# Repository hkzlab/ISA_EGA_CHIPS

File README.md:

# Enhanced Graphics Adapter

## Introduction

This board is and EGA clone based on a reversed **PA-WTEGA** card, based on the chipset by **CHIPS** (P82C435 + P82A436). 

The chipset should be compatible with EGA, CGA, MDA and Hercules standards.

### Disclaimer

I take NO responsibility for what happens if you decide to build and use this card. Your computer might crash, catch fire or be destroyed in other nasty ways.
You're encourauged to take what you deem fit from this, and use it in your projects!

### Configuration

The card as a bank of 5 dipswitches. Dipswitch 1-4 select the card video output mode, dipswitch 5 selects the IO address.

0 means switch open, 1 means closed.

* Jumpers 1-4:
    * 0-1-0-0: MDA Mode (main)
    * 1-0-0-1: CGA 40x25 (main)
    * 1-0-0-0: CGA 80x25 (main)
    * 0-1-1-1: EGA 200 lines (main)
    * 0-1-1-0: EGA 350 lines (main)
    * 1-1-1-1: CGA 40x25 (secondary)
    * 1-1-1-0: CGA 80x25 (secondary)
    * 1-1-0-1: EGA 200 lines (secondary)
    * 1-1-0-0: EGA 350 lines (secondary)
* Jumper 5:
    * 0: I/O address range in 3xx **default**
    * 1: I/O address range in 2xx

**NOTE:** The meaning of each combination is dependant on the bios of the card. This list was taken from the TEVA-2 card's manual.

TODO: Test all the combinations provided in the TEVA-2 card manual

### Functionalities

✅ means I tested the functionality and it works, ❌ means I tested the functionality and found issues, ? means that the functionality has yet to be tested.

* [✅] Display checkup with CheckIt (5154/EGA monitor)
* [✅] Display checkup with CheckIt (5153/CGA monitor)
* [?] Display checkup with CheckIt (5151/MDA monitor)
* [?] Display checkup with CheckIt (Hercules mode)
* [?] Feature Connector
* [?] Light pen input

## Bill of Materials

| Component         | Qty | Type / Value        |
| ----------------- | --- | ------------------- |
| **TODO**          |     |                     |

You can hardwire `JP1` pins 1-2 and `JP2` pins 2-3.

Connectors `RCA 1` and `RCA 2` are useless unless an expansion for the feature connector is used. You can leave them out.

### BIOS

This board was tested with [Phoenix Video Bios V1.02 for P82C435](bios/Phoenix_video_bios_PA-WTEGA_NMC27C256Q.BIN).

Burn it on a 27C256 and plug it in U10.

### Component substitutions

* U15 and U13 can be substituted with HCT equivalents
* U4 is an 'LS244 in the original card, I noticed an improvement in image stability with a MCE2VGA by using an 'F244 

## Known issues

### General issues

These are issues found with this board, but that are **also present in the original model** I cloned.

* Screen tearing detected in Commander Keen 4 and 5 (also happening on DOSBox configured for EGA, also note [here](http://nerdlypleasures.blogspot.com/2014/09/how-many-fps-dos-games-and-framerates.html): `The use of 35 frames, even in a 16-color game like Keen, demonstrates that ID was using VGA, not EGA, to develop the game` ). It can be fixed in-game by enabling the "Fix Jerky Motion" option in the config screen.
* Minor graphical glitches (flickering at top of the screen) during gameplay in Tom & Jerry CAT-astrophe.

### Rev 0.1

* Not really an issue as this is not present in the original card I cloned, but might be worth to add a jumper that can physically connect pin 2 of the DB9 connector to GND and not rely only on the jumper configuration, when using the card with a CGA monitor.

### Rev 0

* Some traces stub are left near the edge connector
* Some traces for sensitive sync signals are routed under the oscillators

## TODO

* Testing...

## Credits

Thanks to [Sergey Kiselev](https://github.com/skiselev) for his symbol/footprint library!

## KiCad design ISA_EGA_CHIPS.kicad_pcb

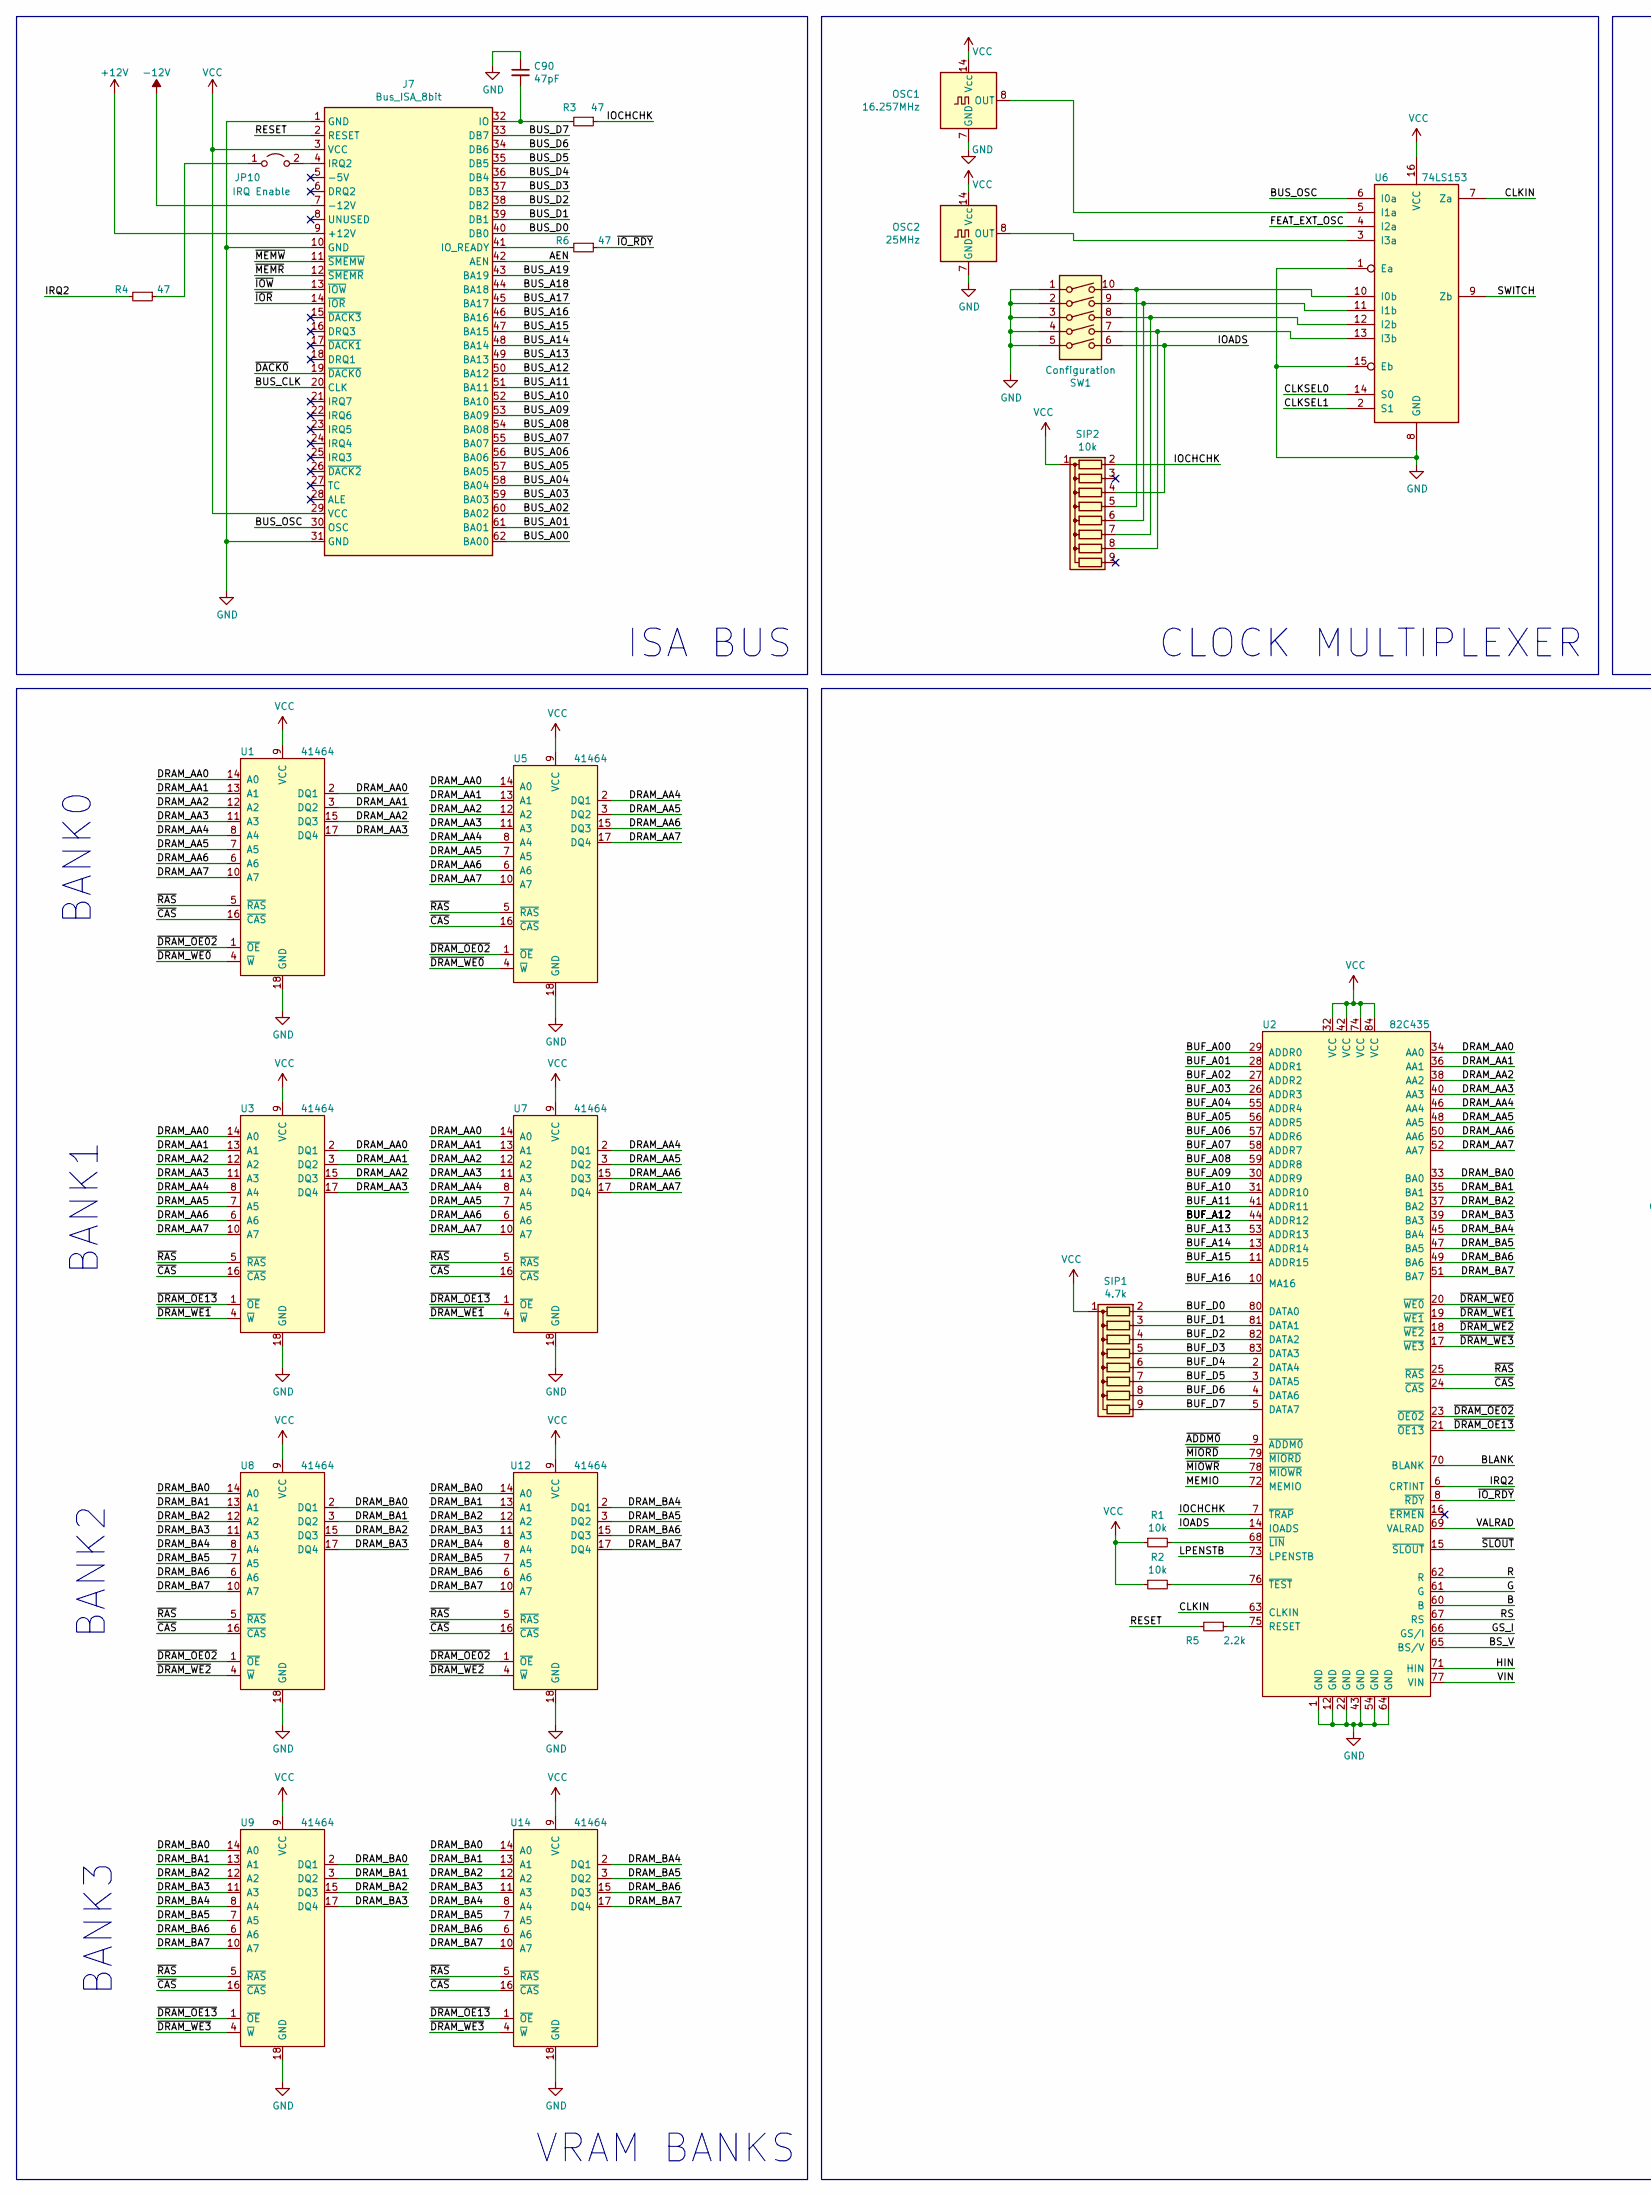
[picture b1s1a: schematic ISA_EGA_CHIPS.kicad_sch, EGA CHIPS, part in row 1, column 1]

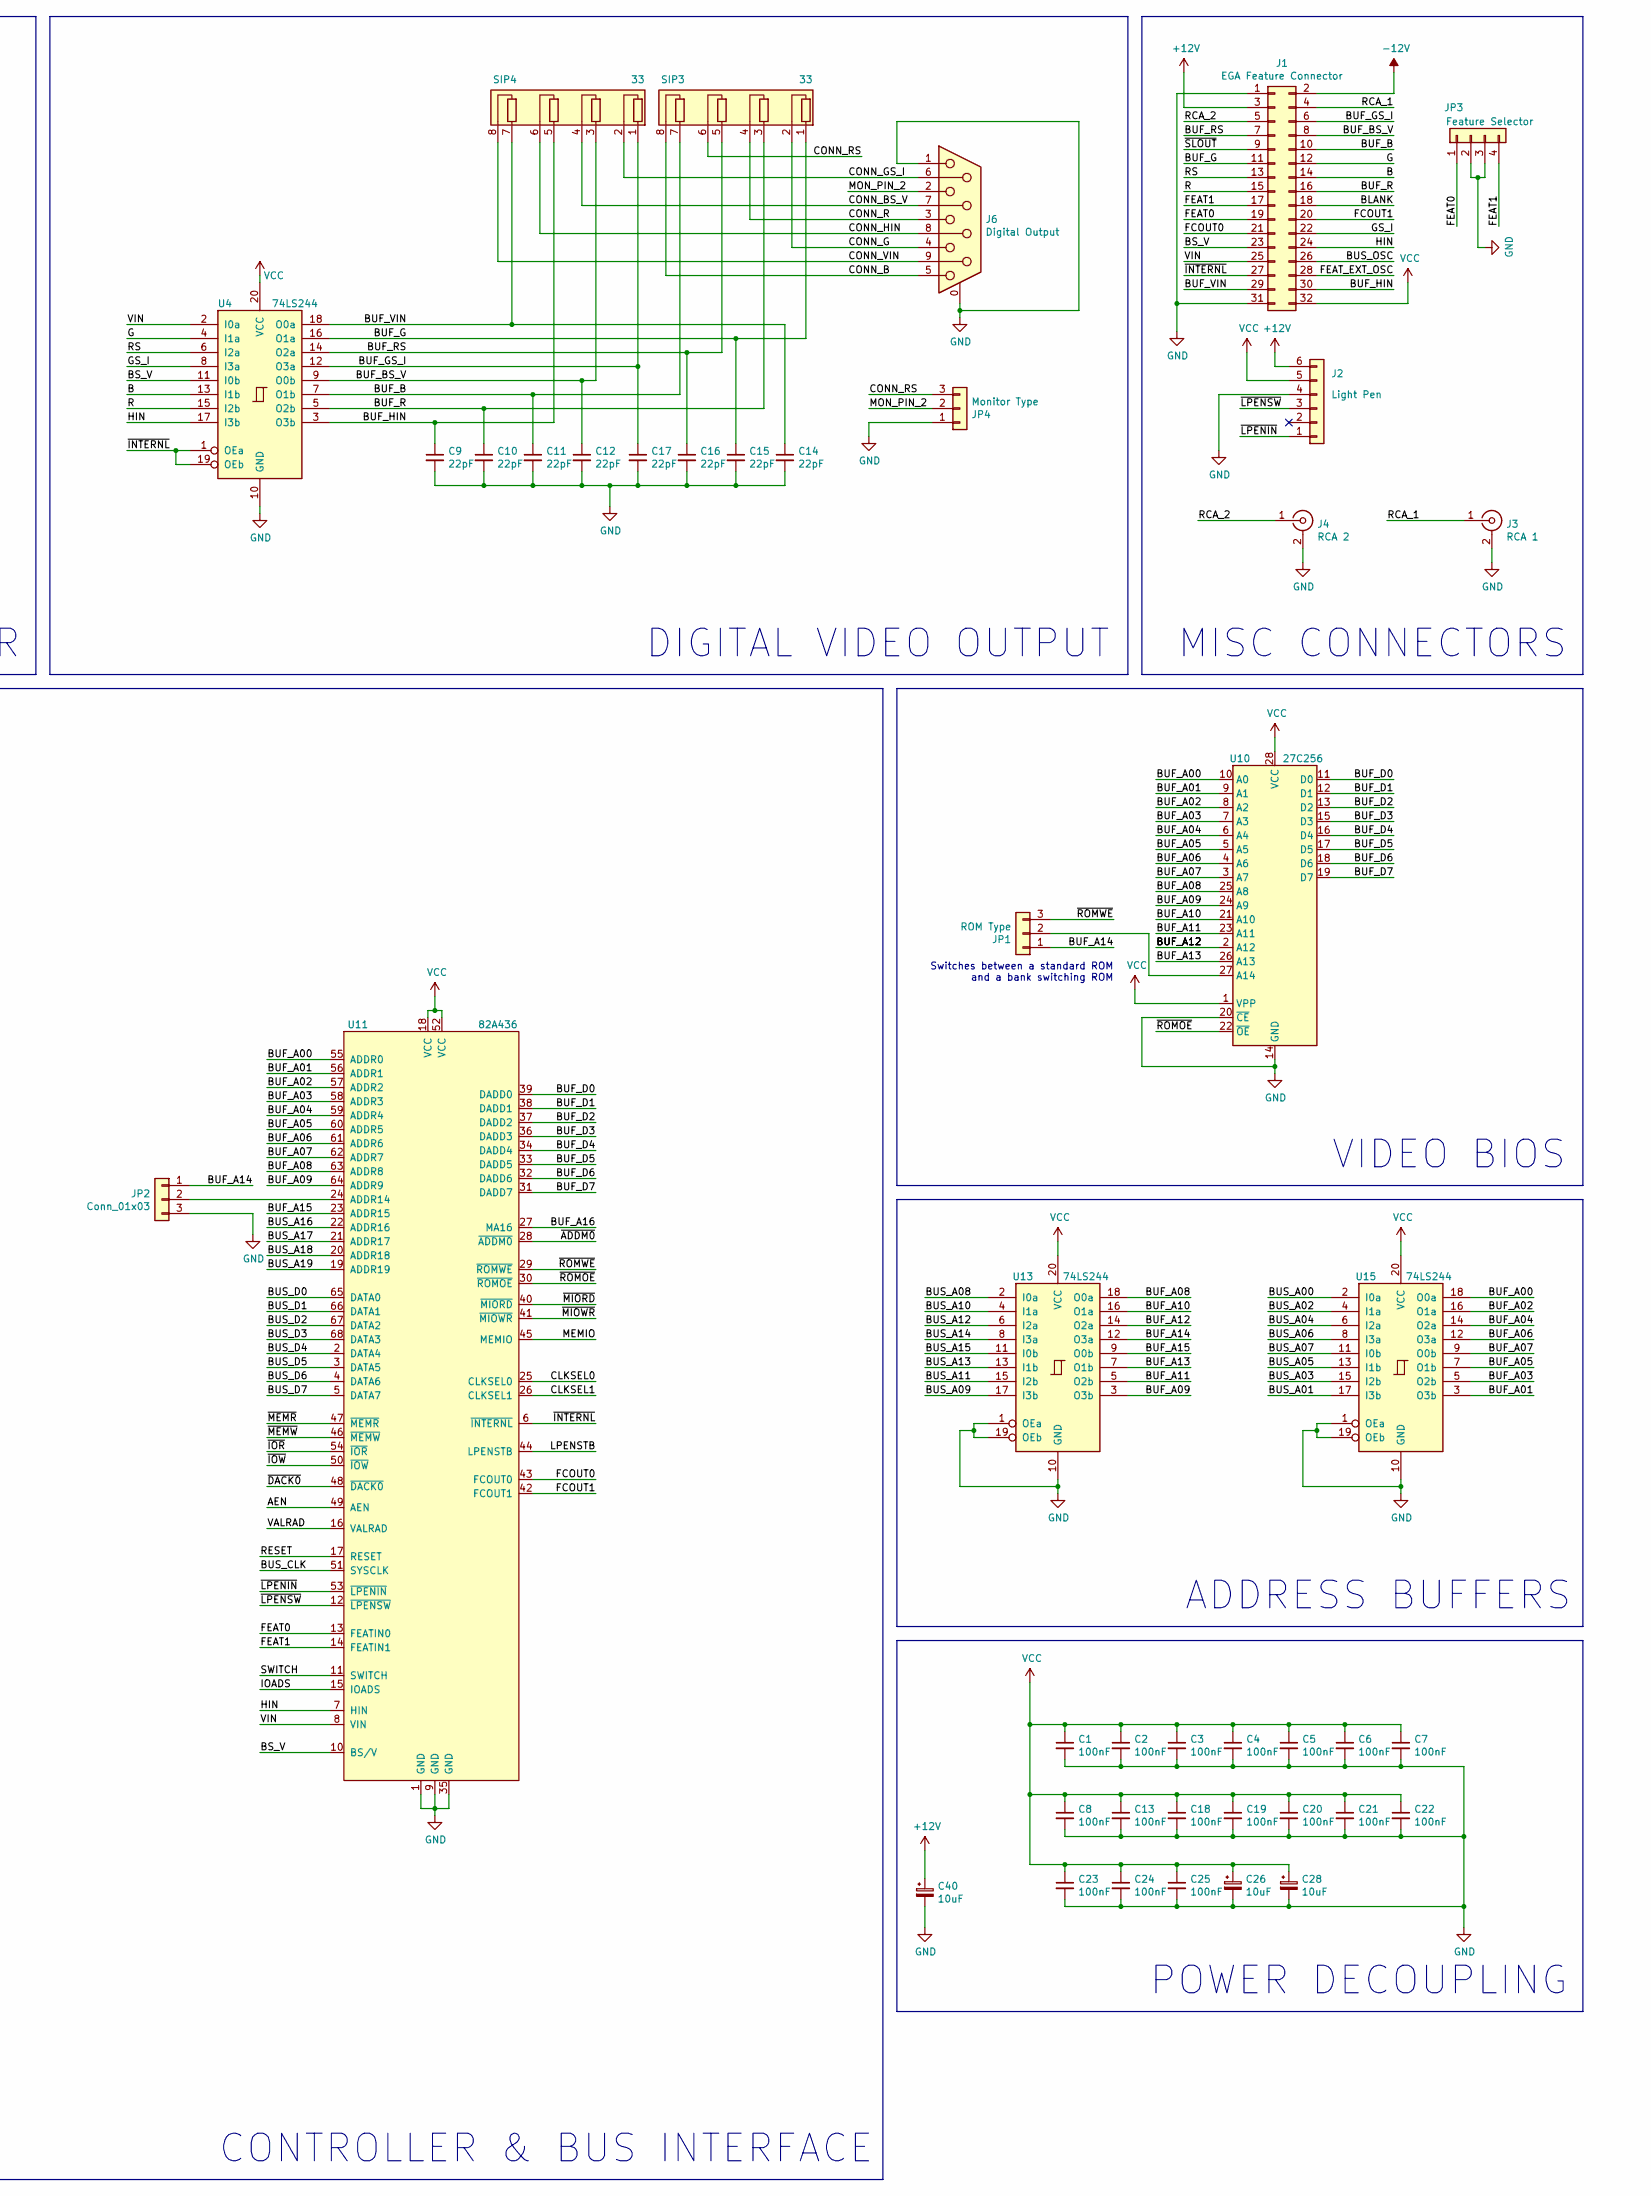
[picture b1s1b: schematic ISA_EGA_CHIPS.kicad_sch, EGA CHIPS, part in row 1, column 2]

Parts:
C1, C2, C3, C4, C5, C6, C7, C8, C13, C18, C19, C20, C21, C22, C23, C24, C25: 100nF; C_Disc_D4.3mm_W1.9mm_P5.00mm
C9, C10, C11, C12, C14, C15, C16, C17: 22pF; C_Disc_D4.3mm_W1.9mm_P5.00mm
C26, C28, C40: 10uF; CP_Radial_D5.0mm_P2.50mm
C90: 47pF; C_Disc_D4.3mm_W1.9mm_P5.00mm
J1: EGA Feature Connector; PinHeader_2x16_P2.54mm_Vertical
J2: Light Pen; PinHeader_1x06_P2.54mm_Vertical
J3: RCA 1; Conn_RCA_Right
J4: RCA 2; Conn_RCA_Right
J6: Digital Output; DSUB-9_Female_Horizontal_P2.77x2.84mm_EdgePinOffset7.70mm_H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
J7: Bus_ISA_8bit; Conn_Edge_PCB_ISA8
JP1: ROM Type; PinHeader_1x03_P2.54mm_Vertical
JP2: Conn_01x03; PinHeader_1x03_P2.54mm_Vertical
JP3: Feature Selector; PinHeader_1x04_P2.54mm_Vertical
JP4: Monitor Type; PinHeader_1x03_P2.54mm_Vertical
JP10: IRQ Enable; PinHeader_1x02_P2.54mm_Vertical
OSC1: 16.257MHz; Oscillator_DIP-14-8
OSC2: 25MHz; Oscillator_DIP-14-8
R1, R2: 10k; R_Axial_DIN0207_L6.3mm_D2.5mm_P7.62mm_Horizontal
R3, R4, R6: 47; R_Axial_DIN0207_L6.3mm_D2.5mm_P7.62mm_Horizontal
R5: 2.2k; R_Axial_DIN0207_L6.3mm_D2.5mm_P7.62mm_Horizontal
SIP1: 4.7k; R_Array_SIP9
SIP2: 10k; R_Array_SIP9
SIP3, SIP4: 33; R_Array_SIP8
SW1: Configuration; DIP-10_W7.62mm_Socket
U1, U3, U5, U7, U8, U9, U12, U14: 41464; DIP-18_W7.62mm
U2: 82C435; PLCC-84_THT-Socket
U4, U13, U15: 74LS244; DIP-20_W7.62mm
U6: 74LS153; DIP-16_W7.62mm
U10: 27C256; DIP-28_W15.24mm
U11: 82A436; PLCC-68_THT-Socket

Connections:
+12V: C40.1, J1.3, J2.6, J7.9 (+12V)
-12V: J1.2, J7.7 (-12V)
/AEN: J7.42 (AEN), U11.49 (AEN)
/B: J1.14, U2.60 (B), U4.13 (I1b)
/BLANK: J1.18, U2.70 (BLANK)
/BS_V: J1.23, U2.65 (BS/V), U4.11 (I0b), U11.10 (BS/V)
/BUF_A00: U2.29 (ADDR0), U10.10 (A0), U11.55 (ADDR0), U15.18 (O0a)
/BUF_A01: U2.28 (ADDR1), U10.9 (A1), U11.56 (ADDR1), U15.3 (O3b)
/BUF_A02: U2.27 (ADDR2), U10.8 (A2), U11.57 (ADDR2), U15.16 (O1a)
/BUF_A03: U2.26 (ADDR3), U10.7 (A3), U11.58 (ADDR3), U15.5 (O2b)
/BUF_A04: U2.55 (ADDR4), U10.6 (A4), U11.59 (ADDR4), U15.14 (O2a)
/BUF_A05: U2.56 (ADDR5), U10.5 (A5), U11.60 (ADDR5), U15.7 (O1b)
/BUF_A06: U2.57 (ADDR6), U10.4 (A6), U11.61 (ADDR6), U15.12 (O3a)
/BUF_A07: U2.58 (ADDR7), U10.3 (A7), U11.62 (ADDR7), U15.9 (O0b)
/BUF_A08: U2.59 (ADDR8), U10.25 (A8), U11.63 (ADDR8), U13.18 (O0a)
/BUF_A09: U2.30 (ADDR9), U10.24 (A9), U11.64 (ADDR9), U13.3 (O3b)
/BUF_A10: U2.31 (ADDR10), U10.21 (A10), U13.16 (O1a)
/BUF_A11: U2.41 (ADDR11), U10.23 (A11), U13.5 (O2b)
/BUF_A12: U2.44 (ADDR12), U10.2 (A12), U13.14 (O2a)
/BUF_A13: U2.53 (ADDR13), U10.26 (A13), U13.7 (O1b)
/BUF_A14: JP1.1, JP2.1, U2.13 (ADDR14), U13.12 (O3a)
/BUF_A15: U2.11 (ADDR15), U11.23 (ADDR15), U13.9 (O0b)
/BUF_A16: U2.10 (MA16), U11.27 (MA16)
/BUF_B: C11.1, J1.10, SIP3.7 (R4.1), U4.7 (O1b)
/BUF_BS_V: C12.1, J1.8, SIP4.3 (R2.1), U4.9 (O0b)
/BUF_D0: SIP1.2 (R1), U2.80 (DATA0), U10.11 (D0), U11.39 (DADD0)
/BUF_D1: SIP1.3 (R2), U2.81 (DATA1), U10.12 (D1), U11.38 (DADD1)
/BUF_D2: SIP1.4 (R3), U2.82 (DATA2), U10.13 (D2), U11.37 (DADD2)
/BUF_D3: SIP1.5 (R4), U2.83 (DATA3), U10.15 (D3), U11.36 (DADD3)
/BUF_D4: SIP1.6 (R5), U2.2 (DATA4), U10.16 (D4), U11.34 (DADD4)
/BUF_D5: SIP1.7 (R6), U2.3 (DATA5), U10.17 (D5), U11.33 (DADD5)
/BUF_D6: SIP1.8 (R7), U2.4 (DATA6), U10.18 (D6), U11.32 (DADD6)
/BUF_D7: SIP1.9 (R8), U2.5 (DATA7), U10.19 (D7), U11.31 (DADD7)
/BUF_G: C15.1, J1.11, SIP3.1 (R1.1), U4.16 (O1a)
/BUF_GS_I: C17.1, J1.6, SIP4.1 (R1.1), U4.12 (O3a)
/BUF_HIN: C9.1, J1.30, SIP4.5 (R3.1), U4.3 (O3b)
/BUF_R: C10.1, J1.16, SIP3.3 (R2.1), U4.5 (O2b)
/BUF_RS: C16.1, J1.7, SIP3.5 (R3.1), U4.14 (O2a)
/BUF_VIN: C14.1, J1.29, SIP4.7 (R4.1), U4.18 (O0a)
/BUS_A00: J7.62 (BA00), U15.2 (I0a)
/BUS_A01: J7.61 (BA01), U15.17 (I3b)
/BUS_A02: J7.60 (BA02), U15.4 (I1a)
/BUS_A03: J7.59 (BA03), U15.15 (I2b)
/BUS_A04: J7.58 (BA04), U15.6 (I2a)
/BUS_A05: J7.57 (BA05), U15.13 (I1b)
/BUS_A06: J7.56 (BA06), U15.8 (I3a)
/BUS_A07: J7.55 (BA07), U15.11 (I0b)
/BUS_A08: J7.54 (BA08), U13.2 (I0a)
/BUS_A09: J7.53 (BA09), U13.17 (I3b)
/BUS_A10: J7.52 (BA10), U13.4 (I1a)
/BUS_A11: J7.51 (BA11), U13.15 (I2b)
/BUS_A12: J7.50 (BA12), U13.6 (I2a)
/BUS_A13: J7.49 (BA13), U13.13 (I1b)
/BUS_A14: J7.48 (BA14), U13.8 (I3a)
/BUS_A15: J7.47 (BA15), U13.11 (I0b)
/BUS_A16: J7.46 (BA16), U11.22 (ADDR16)
/BUS_A17: J7.45 (BA17), U11.21 (ADDR17)
/BUS_A18: J7.44 (BA18), U11.20 (ADDR18)
/BUS_A19: J7.43 (BA19), U11.19 (ADDR19)
/BUS_CLK: J7.20 (CLK), U11.51 (SYSCLK)
/BUS_D0: J7.40 (DB0), U11.65 (DATA0)
/BUS_D1: J7.39 (DB1), U11.66 (DATA1)
/BUS_D2: J7.38 (DB2), U11.67 (DATA2)
/BUS_D3: J7.37 (DB3), U11.68 (DATA3)
/BUS_D4: J7.36 (DB4), U11.2 (DATA4)
/BUS_D5: J7.35 (DB5), U11.3 (DATA5)
/BUS_D6: J7.34 (DB6), U11.4 (DATA6)
/BUS_D7: J7.33 (DB7), U11.5 (DATA7)
/BUS_OSC: J1.26, J7.30 (OSC), U6.6 (I0a)
/CLKIN: U2.63 (CLKIN), U6.7 (Za)
/CLKSEL0: U6.14 (S0), U11.25 (CLKSEL0)
/CLKSEL1: U6.2 (S1), U11.26 (CLKSEL1)
/CONN_B: J6.5, SIP3.8 (R4.2)
/CONN_BS_V: J6.7, SIP4.4 (R2.2)
/CONN_G: J6.4, SIP3.2 (R1.2)
/CONN_GS_I: J6.6, SIP4.2 (R1.2)
/CONN_HIN: J6.8, SIP4.6 (R3.2)
/CONN_R: J6.3, SIP3.4 (R2.2)
/CONN_RS: JP4.3, SIP3.6 (R3.2)
/CONN_VIN: J6.9, SIP4.8 (R4.2)
/DRAM_AA0: U1.2 (DQ1), U1.14 (A0), U2.34 (AA0), U3.2 (DQ1), U3.14 (A0), U5.14 (A0), U7.14 (A0)
/DRAM_AA1: U1.3 (DQ2), U1.13 (A1), U2.36 (AA1), U3.3 (DQ2), U3.13 (A1), U5.13 (A1), U7.13 (A1)
/DRAM_AA2: U1.12 (A2), U1.15 (DQ3), U2.38 (AA2), U3.12 (A2), U3.15 (DQ3), U5.12 (A2), U7.12 (A2)
/DRAM_AA3: U1.11 (A3), U1.17 (DQ4), U2.40 (AA3), U3.11 (A3), U3.17 (DQ4), U5.11 (A3), U7.11 (A3)
/DRAM_AA4: U1.8 (A4), U2.46 (AA4), U3.8 (A4), U5.2 (DQ1), U5.8 (A4), U7.2 (DQ1), U7.8 (A4)
/DRAM_AA5: U1.7 (A5), U2.48 (AA5), U3.7 (A5), U5.3 (DQ2), U5.7 (A5), U7.3 (DQ2), U7.7 (A5)
/DRAM_AA6: U1.6 (A6), U2.50 (AA6), U3.6 (A6), U5.6 (A6), U5.15 (DQ3), U7.6 (A6), U7.15 (DQ3)
/DRAM_AA7: U1.10 (A7), U2.52 (AA7), U3.10 (A7), U5.10 (A7), U5.17 (DQ4), U7.10 (A7), U7.17 (DQ4)
/DRAM_BA0: U2.33 (BA0), U8.2 (DQ1), U8.14 (A0), U9.2 (DQ1), U9.14 (A0), U12.14 (A0), U14.14 (A0)
/DRAM_BA1: U2.35 (BA1), U8.3 (DQ2), U8.13 (A1), U9.3 (DQ2), U9.13 (A1), U12.13 (A1), U14.13 (A1)
/DRAM_BA2: U2.37 (BA2), U8.12 (A2), U8.15 (DQ3), U9.12 (A2), U9.15 (DQ3), U12.12 (A2), U14.12 (A2)
/DRAM_BA3: U2.39 (BA3), U8.11 (A3), U8.17 (DQ4), U9.11 (A3), U9.17 (DQ4), U12.11 (A3), U14.11 (A3)
/DRAM_BA4: U2.45 (BA4), U8.8 (A4), U9.8 (A4), U12.2 (DQ1), U12.8 (A4), U14.2 (DQ1), U14.8 (A4)
/DRAM_BA5: U2.47 (BA5), U8.7 (A5), U9.7 (A5), U12.3 (DQ2), U12.7 (A5), U14.3 (DQ2), U14.7 (A5)
/DRAM_BA6: U2.49 (BA6), U8.6 (A6), U9.6 (A6), U12.6 (A6), U12.15 (DQ3), U14.6 (A6), U14.15 (DQ3)
/DRAM_BA7: U2.51 (BA7), U8.10 (A7), U9.10 (A7), U12.10 (A7), U12.17 (DQ4), U14.10 (A7), U14.17 (DQ4)
/FCOUT0: J1.21, U11.43 (FCOUT0)
/FCOUT1: J1.20, U11.42 (FCOUT1)
/FEAT0: J1.19, JP3.1, U11.13 (FEATIN0)
/FEAT1: J1.17, JP3.4, U11.14 (FEATIN1)
/FEAT_EXT_OSC: J1.28, U6.4 (I2a)
/G: J1.12, U2.61 (G), U4.4 (I1a)
/GS_I: J1.22, U2.66 (GS/I), U4.8 (I3a)
/HIN: J1.24, U2.71 (HIN), U4.17 (I3b), U11.7 (HIN)
/IOADS: SIP2.4 (R3), SW1.6, U2.14 (IOADS), U11.15 (IOADS)
/IOCHCHK: R3.1, SIP2.2 (R1), U2.7 (~TRAP)
/IRQ2: R4.2, U2.6 (CRTINT)
/LPENSTB: U2.73 (LPENSTB), U11.44 (LPENSTB)
/MEMIO: U2.72 (MEMIO), U11.45 (MEMIO)
/MON_PIN_2: J6.2, JP4.2
/R: J1.15, U2.62 (R), U4.15 (I2b)
/RCA_1: J1.4, J3.1 (In)
/RCA_2: J1.5, J4.1 (In)
/RESET: J7.2 (RESET), R5.2, U11.17 (RESET)
/RS: J1.13, U2.67 (RS), U4.6 (I2a)
/SWITCH: U6.9 (Zb), U11.11 (SWITCH)
/VALRAD: U2.69 (VALRAD), U11.16 (VALRAD)
/VIN: J1.25, U2.77 (VIN), U4.2 (I0a), U11.8 (VIN)
/~ADDM0: U2.9 (~ADDM0), U11.28 (~ADDM0)
/~CAS: U1.16 (~CAS), U2.24 (~CAS), U3.16 (~CAS), U5.16 (~CAS), U7.16 (~CAS), U8.16 (~CAS), U9.16 (~CAS), U12.16 (~CAS), U14.16 (~CAS)
/~DACK0: J7.19 (~DACK0), U11.48 (~DACK0)
/~DRAM_OE02: U1.1 (~OE), U2.23 (~OE02), U5.1 (~OE), U8.1 (~OE), U12.1 (~OE)
/~DRAM_OE13: U2.21 (~OE13), U3.1 (~OE), U7.1 (~OE), U9.1 (~OE), U14.1 (~OE)
/~DRAM_WE0: U1.4 (~W), U2.20 (~WE0), U5.4 (~W)
/~DRAM_WE1: U2.19 (~WE1), U3.4 (~W), U7.4 (~W)
/~DRAM_WE2: U2.18 (~WE2), U8.4 (~W), U12.4 (~W)
/~DRAM_WE3: U2.17 (~WE3), U9.4 (~W), U14.4 (~W)
/~INTERNL: J1.27, U4.1 (OEa), U4.19 (OEb), U11.6 (~INTERNL)
/~IOR: J7.14 (~IOR), U11.54 (~IOR)
/~IOW: J7.13 (~IOW), U11.50 (~IOW)
/~IO_RDY: R6.1, U2.8 (~RDY)
/~LPENIN: J2.1, U11.53 (~LPENIN)
/~LPENSW: J2.3, U11.12 (~LPENSW)
/~MEMR: J7.12 (~SMEMR), U11.47 (~MEMR)
/~MEMW: J7.11 (~SMEMW), U11.46 (~MEMW)
/~MIORD: U2.79 (~MIORD), U11.40 (~MIORD)
/~MIOWR: U2.78 (~MIOWR), U11.41 (~MIOWR)
/~RAS: U1.5 (~RAS), U2.25 (~RAS), U3.5 (~RAS), U5.5 (~RAS), U7.5 (~RAS), U8.5 (~RAS), U9.5 (~RAS), U12.5 (~RAS), U14.5 (~RAS)
/~ROMOE: U10.22 (~OE), U11.30 (~ROMOE)
/~ROMWE: JP1.3, U11.29 (~ROMWE)
/~SLOUT: J1.9, U2.15 (~SLOUT)
GND: C1.2, C2.2, C3.2, C4.2, C5.2, C6.2, C7.2, C8.2, C9.2, C10.2, C11.2, C12.2, C13.2, C14.2, C15.2, C16.2, C17.2, C18.2, C19.2, C20.2, C21.2, C22.2, C23.2, C24.2, C25.2, C26.2, C28.2, C40.2, C90.1, J1.1, J1.31, J2.4, J3.2 (Ext), J4.2 (Ext), J6.0 (PAD), J6.1, J7.1 (GND), J7.10 (GND), J7.31 (GND), JP2.3, JP3.2, JP3.3, JP4.1, OSC1.7 (GND), OSC2.7 (GND), SW1.1, SW1.2, SW1.3, SW1.4, SW1.5, U1.18 (GND), U2.1 (GND), U2.12 (GND), U2.22 (GND), U2.43 (GND), U2.54 (GND), U2.64 (GND), U3.18 (GND), U4.10 (GND), U5.18 (GND), U6.1 (Ea), U6.8 (GND), U6.15 (Eb), U7.18 (GND), U8.18 (GND), U9.18 (GND), U10.14 (GND), U10.20 (~CE), U11.1 (GND), U11.9 (GND), U11.35 (GND), U12.18 (GND), U13.1 (OEa), U13.10 (GND), U13.19 (OEb), U14.18 (GND), U15.1 (OEa), U15.10 (GND), U15.19 (OEb)
unnamed: C90.2, J7.32 (IO), R3.2
unnamed: J7.4 (IRQ2), JP10.2 (B)
unnamed: J7.41 (IO_READY), R6.2
unnamed: JP1.2, U10.27 (A14)
unnamed: JP2.2, U11.24 (ADDR14)
unnamed: JP10.1 (A), R4.1
unnamed: OSC1.8 (OUT), U6.5 (I1a)
unnamed: OSC2.8 (OUT), U6.3 (I3a)
unnamed: R1.2, U2.68 (~LIN)
unnamed: R2.2, U2.76 (~TEST)
unnamed: R5.1, U2.75 (RESET)
unnamed: SIP2.5 (R4), SW1.10, U6.10 (I0b)
unnamed: SIP2.6 (R5), SW1.9, U6.11 (I1b)
unnamed: SIP2.7 (R6), SW1.8, U6.12 (I2b)
unnamed: SIP2.8 (R7), SW1.7, U6.13 (I3b)
VCC: C1.1, C2.1, C3.1, C4.1, C5.1, C6.1, C7.1, C8.1, C13.1, C18.1, C19.1, C20.1, C21.1, C22.1, C23.1, C24.1, C25.1, C26.1, C28.1, J1.32, J2.5, J7.3 (VCC), J7.29 (VCC), OSC1.14 (Vcc), OSC2.14 (Vcc), R1.1, R2.1, SIP1.1 (common), SIP2.1 (common), U1.9 (VCC), U2.32 (VCC), U2.42 (VCC), U2.74 (VCC), U2.84 (VCC), U3.9 (VCC), U4.20 (VCC), U5.9 (VCC), U6.16 (VCC), U7.9 (VCC), U8.9 (VCC), U9.9 (VCC), U10.1 (VPP), U10.28 (VCC), U11.18 (VCC), U11.52 (VCC), U12.9 (VCC), U13.20 (VCC), U14.9 (VCC), U15.20 (VCC)

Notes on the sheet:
BANK3
BANK1
BANK0
CLOCK MULTIPLEXER
CONTROLLER & BUS INTERFACE
Switches between a standard ROM and a bank switching ROM
DIGITAL VIDEO OUTPUT
BANK2
VIDEO BIOS
ISA BUS
MISC CONNECTORS
VRAM BANKS
ADDRESS BUFFERS
POWER DECOUPLING

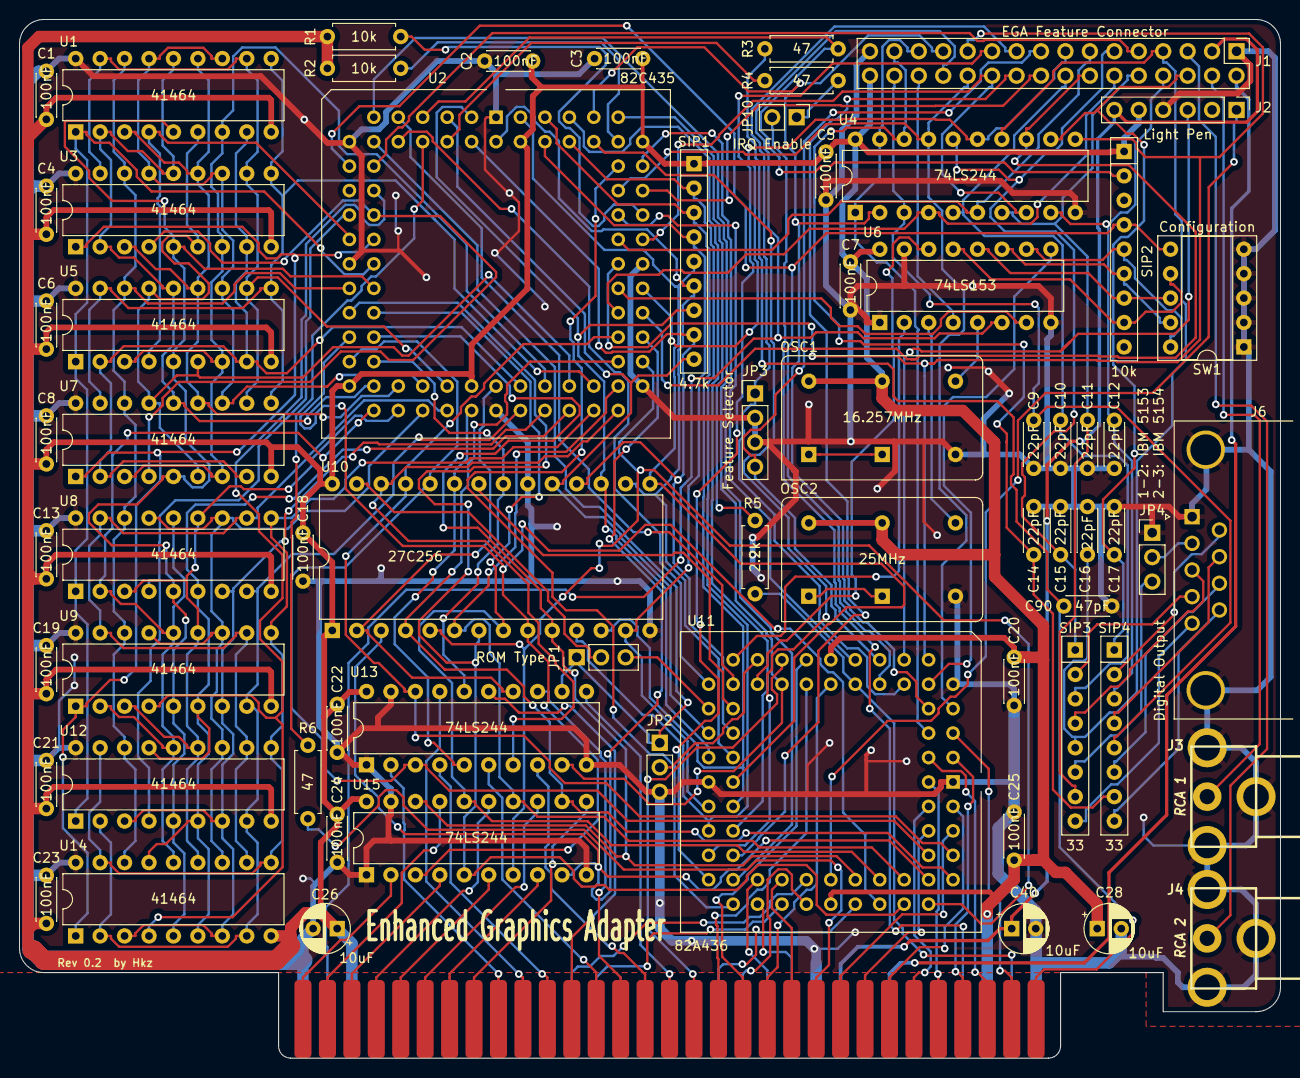
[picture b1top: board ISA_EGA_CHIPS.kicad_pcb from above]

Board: 2 copper layers, 131.1 x 108.0 mm, 68 parts (0 on the bottom side), 158 nets.

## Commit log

2021-06-14 Basic files
2021-06-14 Begin defining 82C435
2021-06-14 More pins for 82C435
2021-06-14 82C435 symbol
2021-06-14 Begin symbol for 82A436
2021-06-15 Add symbol for 82A436
2021-06-15 Added symbol for 41464
2021-06-15 Add RAM banks
2021-06-15 Added the other remaining ICs
2021-06-15 Added resistor packs
2021-06-15 Additional devices added to the schematic
2021-06-15 Add resistors
2021-06-15 Add jumpers
2021-06-15 More components
2021-06-15 Add first capacitors
2021-06-15 Added all missing components
2021-06-15 Add number for ISA bus connector
2021-06-15 Connected filter caps a powe supply in bus
2021-06-15 Add some connections
2021-06-15 Add connections for FEAT0/1
2021-06-15 Begin drawing wires for configuration switch decoding
2021-06-15 Removed two wires
2021-06-15 Completed the circuit for the multiplexer
2021-06-15 Moved connector
2021-06-15 Some more wires
2021-06-15 Some more wiring
2021-06-16 Fix IOCHCHK signal
2021-06-16 Fix IRQ2 signal
2021-06-16 Connect some more resistors
2021-06-16 Add bus connections
2021-06-16 Fix some more connections
2021-06-17 More connections
2021-06-17 More buffer connections
2021-06-17 Add another buffered address line
2021-06-17 Fix symbol, add other addresses
2021-06-17 More bus connections
2021-06-17 Some more connections
2021-06-17 Begin connecting data bus
2021-06-17 Add buffered data lines
2021-06-18 Connect more bus lines
2021-06-18 Add RGB to buffer connections
2021-06-18 Reorganize ram banks
2021-06-18 Connected addresses of first ram bank
2021-06-18 More RAM data bus connections
2021-06-18 Begin populating output connections
2021-06-18 First revision of the schematic
2021-06-18 Move around some resistors
2021-06-18 Add some notes
2021-06-18 Move around some components
2021-06-18 Fix some weirdness in the feature and light pen connector
2021-06-18 Add a jumper to disconnect IRQ2
2021-06-18 Add extra symbols and footprints
2021-06-18 Begin assigning some footprints
2021-06-18 Assign some more sockets
2021-06-18 Assigned footprints
2021-06-18 Place some components
2021-06-18 Place some more components
2021-06-18 Placed all components
2021-06-18 Draw basic power traces
2021-06-18 First board render
2021-06-19 Add silkscreen
2021-06-19 Cleaned board, redone power traces
2021-06-19 moved around some components
2021-06-19 Redone some power traces
2021-06-19 Change some more traces
2021-06-19 Added keepout areas on connector
2021-06-19 Resized keepout areas
2021-06-19 Rerouted power traces
2021-06-19 redraw some traces
2021-06-19 Changed silkscreen
2021-06-25 Add gerbers
2021-07-05 Some track cosmetic fixes
2021-07-05 Move EGA Feature Connector silkscreen
2021-07-06 Other silkscreen fixes
2021-07-06 Reroute some traces
2021-07-06 Add README and pictures
2021-07-06 Rerouted some traces
2021-07-06 Better ground plane
2021-07-06 Some more vias
2021-07-08 Add some more grounding
2021-07-08 Update grounding
2021-07-08 Add more grounding
2021-07-19 Fix typo
2021-07-20 Add bio menace guy!
2021-07-27 Add rev 0.1 gerbers
2021-08-01 Add onboard connection for GND on pin 2
2021-08-01 Add another bios version
2021-08-01 Added some silkscreen notes
2021-08-03 Remove dipswitch config from README
2021-08-03 Additional bios files
2021-08-03 Add bios version 1.00
2021-08-09 Add notes
2021-08-10 Updated readme and photo
2021-08-10 Update note in readme
2021-08-16 Add known issue to readme
2021-08-25 Update README with known issues
2021-08-25 Additional notes
2021-08-25 More notes
2021-09-06 Add further notes to readme
2021-11-09 Updated KiCad url
2023-10-20 Import project into KiCad 7
2024-01-21 Mention Hercules mode in the README
2024-01-21 Formatting
